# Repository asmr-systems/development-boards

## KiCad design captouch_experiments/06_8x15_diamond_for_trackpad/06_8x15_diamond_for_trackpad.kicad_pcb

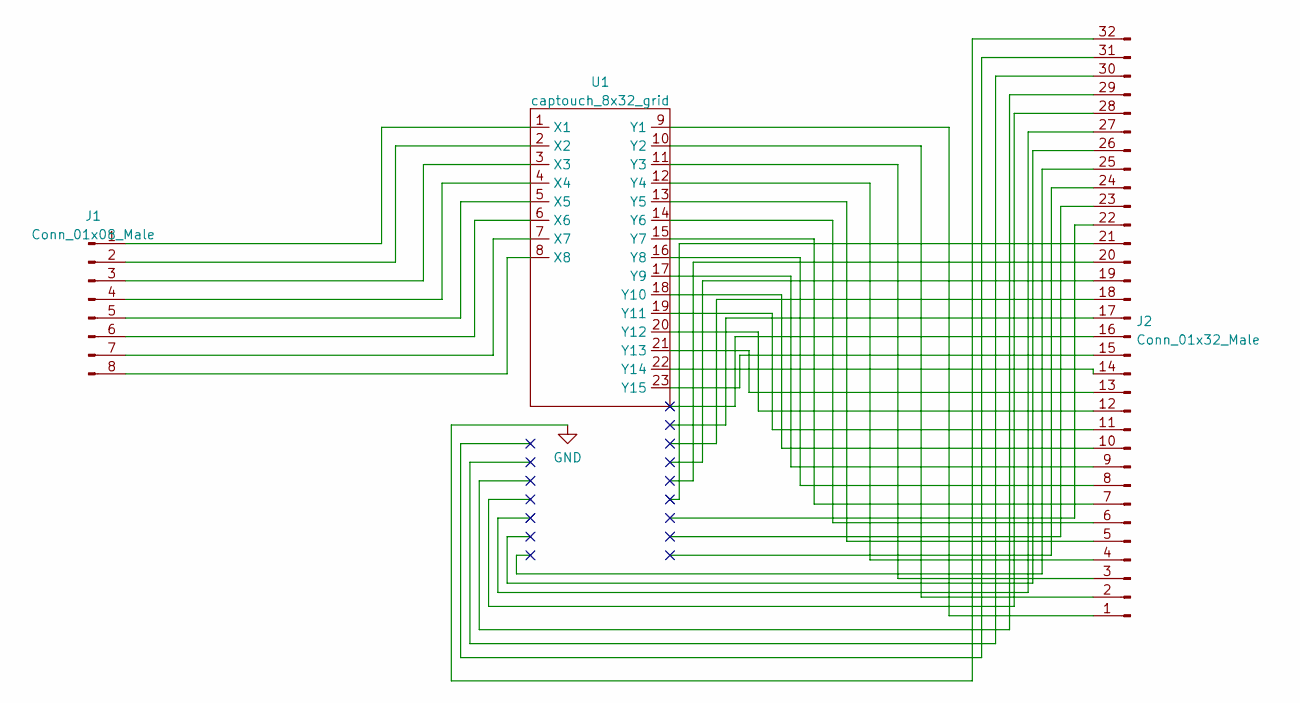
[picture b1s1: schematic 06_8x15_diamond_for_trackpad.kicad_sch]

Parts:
J1: Conn_01x08_Male; Conn_FFC_1x8_0.5mm_Molex_5019510830
J2: Conn_01x32_Male; Conn_FFC_1x32_0.5mm_Molex_5019513210
U1: captouch_8x32_grid; captouch_8x15_diamond_hatched_doubled

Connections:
GND: J2.32
unnamed: J1.1, U1.1 (X1)
unnamed: J1.2, U1.2 (X2)
unnamed: J1.3, U1.3 (X3)
unnamed: J1.4, U1.4 (X4)
unnamed: J1.5, U1.5 (X5)
unnamed: J1.6, U1.6 (X6)
unnamed: J1.7, U1.7 (X7)
unnamed: J1.8, U1.8 (X8)
unnamed: J2.1, U1.9 (Y1)
unnamed: J2.2, U1.10 (Y2)
unnamed: J2.3, U1.11 (Y3)
unnamed: J2.4, U1.12 (Y4)
unnamed: J2.5, U1.13 (Y5)
unnamed: J2.6, U1.14 (Y6)
unnamed: J2.7, U1.15 (Y7)
unnamed: J2.8, U1.16 (Y8)
unnamed: J2.9, U1.17 (Y9)
unnamed: J2.10, U1.18 (Y10)
unnamed: J2.11, U1.19 (Y11)
unnamed: J2.12, U1.20 (Y12)
unnamed: J2.13, U1.21 (Y13)
unnamed: J2.14, U1.22 (Y14)
unnamed: J2.15, U1.23 (Y15)

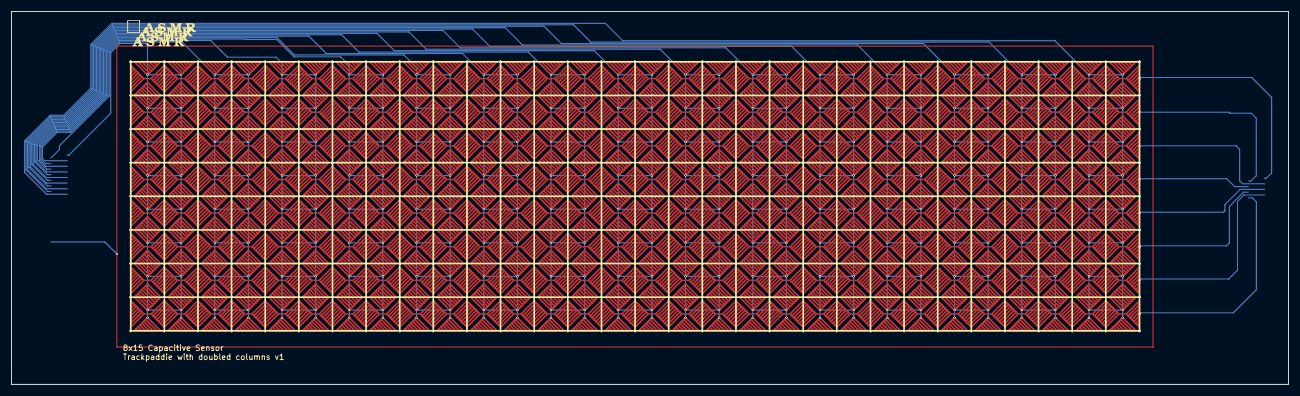
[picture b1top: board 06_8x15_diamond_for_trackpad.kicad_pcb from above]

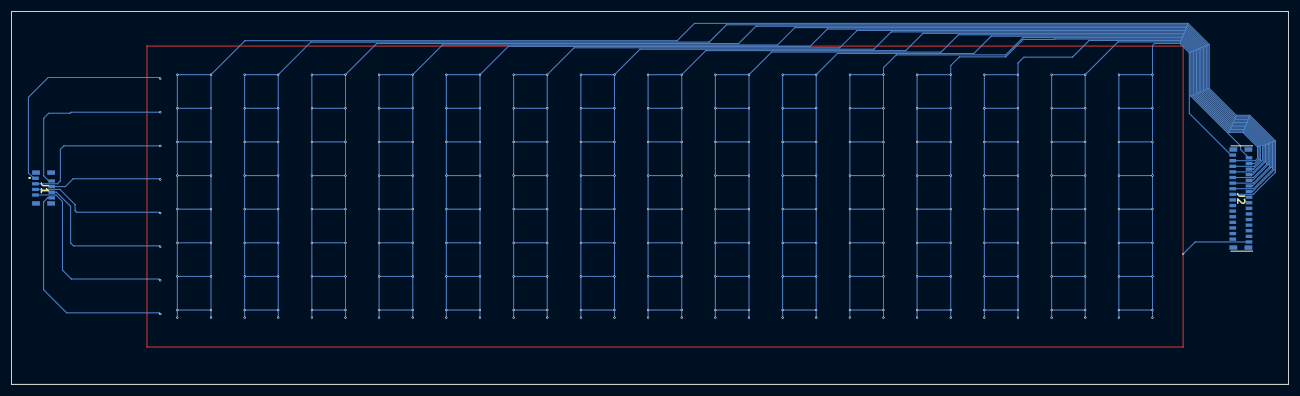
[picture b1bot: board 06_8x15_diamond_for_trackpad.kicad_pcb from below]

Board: 2 copper layers, 227.9 x 66.5 mm, 3 parts (2 on the bottom side), 23 nets.

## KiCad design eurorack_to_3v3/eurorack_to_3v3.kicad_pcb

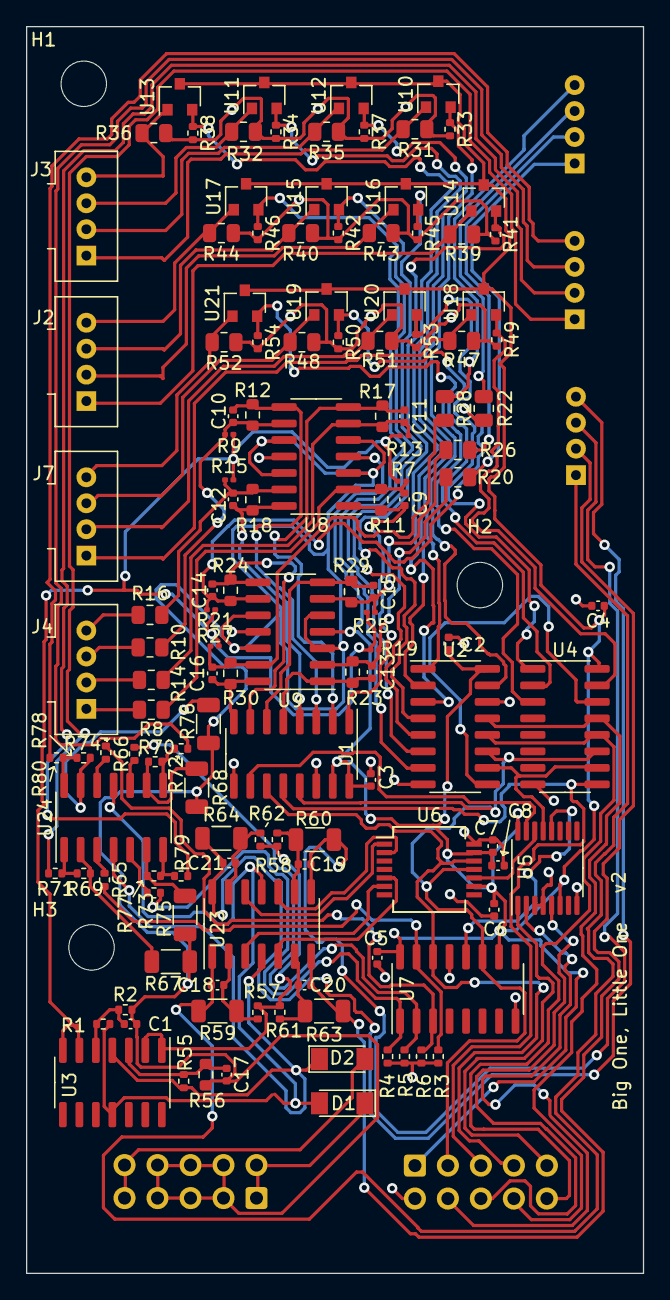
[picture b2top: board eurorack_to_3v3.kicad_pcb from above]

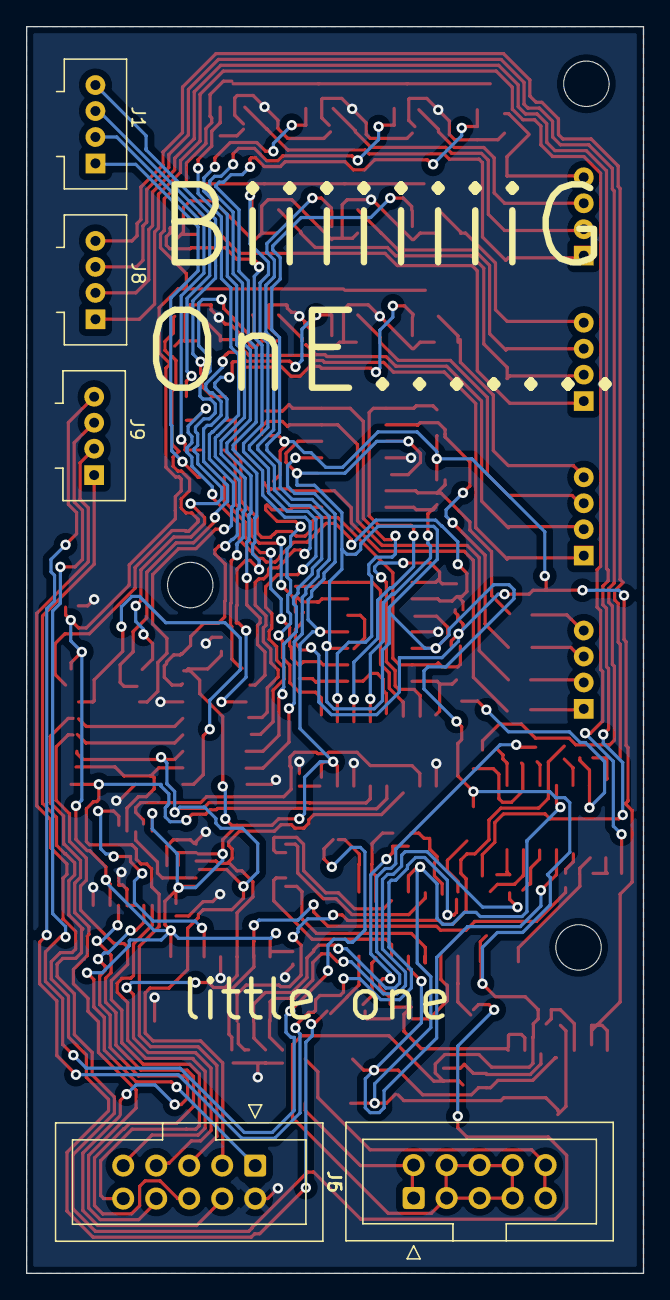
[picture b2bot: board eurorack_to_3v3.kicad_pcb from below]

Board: 2 copper layers, 47.5 x 96.0 mm, 138 parts (5 on the bottom side), 104 nets.

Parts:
C1, C2, C4, C5, C6, C7, C8, C17: 0.1uF; C_0402_1005Metric
C3: 1uF; C_0402_1005Metric
C9, C10, C11, C12, C13, C14, C15, C16, C18, C19, C20, C21: 1nF; C_0402_1005Metric
D1, D2: D; D_MiniMELF
H1, H2, H3: MountingHole; MountingHole_3.5mm
J1: cv_in_2; Connector_TE_AMP_HPI-1735446-4_1x04_P2.00mm_Vertical
J2: gate_in_2; Connector_TE_AMP_HPI-1735446-4_1x04_P2.00mm_Vertical
J3: gate_in_1; Connector_TE_AMP_HPI-1735446-4_1x04_P2.00mm_Vertical
J4: cv_in_1; Connector_TE_AMP_HPI-1735446-4_1x04_P2.00mm_Vertical
J5: Eurorack Power Header; IDC-Header_2x05_P2.54mm_Vertical
J6: Brain Bus; IDC-Header_2x05_P2.54mm_Vertical
J7: gate_in_3; Connector_TE_AMP_HPI-1735446-4_1x04_P2.00mm_Vertical
J8: gate_out; Connector_TE_AMP_HPI-1735446-4_1x04_P2.00mm_Vertical
J9: cv_out; Connector_TE_AMP_HPI-1735446-4_1x04_P2.00mm_Vertical
R1, R3, R4, R5, R6: 10K; R_0402_1005Metric
R2: 50K; R_0402_1005Metric
R7, R9, R13, R15, R19, R21, R25, R27: 200K; R_0201_0603Metric
R8, R10, R14, R16, R20, R22, R26, R28, R31, R32, R35, R36, R39, R40, R43, R44, R47, R48, R51, R52: 100K; R_0805_2012Metric
R11, R12, R17, R18, R23, R24, R29, R30: 33K; R_0603_1608Metric
R33, R34, R37, R38, R41, R42, R45, R46, R49, R50, R53, R54, R71, R72, R79, R80: 1K; R_0402_1005Metric
R55: 12K; R_0402_1005Metric
R56: 3K; R_0603_1608Metric
R57, R58, R61, R62: 11K; R_0402_1005Metric
R59, R60, R63, R64: 24K; R_1206_3216Metric
R65, R66, R73, R74: 23K; R_0402_1005Metric
R67, R68, R75, R76: 39K; R_1206_3216Metric
R69, R70, R77, R78: 56K; R_0402_1005Metric
U1: MCP3208; SOIC-16_3.9x9.9mm_P1.27mm
U2, U4: 74HC589; SOIC-16_3.9x9.9mm_P1.27mm
U3, U24: LM324; SOIC-14_3.9x8.7mm_P1.27mm
U5: 74HC137; TSSOP-16_4.4x5mm_P0.65mm
U6: BH2227FV; SSOP-14_5.3x6.2mm_P0.65mm
U7: 74HC595; SOIC-16_3.9x9.9mm_P1.27mm
U8, U9: MCP6009; SOIC-14_3.9x8.7mm_P1.27mm
U10, U11, U12, U13, U14, U15, U16, U17, U18, U19, U20, U21: MOSFET_RK7002BM; SOT-23
U23: TL074CDT; SOIC-14_3.9x8.7mm_P1.27mm

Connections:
+3V3: C2.1, C3.1, C4.1, C5.1, C6.1, C7.2, C8.1, J6.1, U1.15 (Vref), U1.16 (Vdd), U2.16 (Vcc), U4.16 (Vcc), U5.6 (E2), U5.16 (VCC), U6.9 (VDD), U6.13 (VFS), U7.10 (~SRCLR), U7.16 (VCC), U8.4 (V+), U9.4 (V+), U10.3 (Drain), U11.3 (Drain), U12.3 (Drain), U13.3 (Drain), U14.3 (Drain), U15.3 (Drain), U16.3 (Drain), U17.3 (Drain), U18.3 (Drain), U19.3 (Drain), U20.3 (Drain), U21.3 (Drain)
+12V: D2.1 (K), R55.1, U3.4 (V+), U23.4 (V+), U24.4 (V+)
-12V: D1.2 (A), R1.1, U3.11 (V-), U23.11 (V-), U24.11 (V-)
/3v3_to_cv/CV_3V3_1: U6.6 (AO4), U23.3 (+)
/3v3_to_cv/CV_3V3_2: U6.5 (AO3), U23.5 (+)
/3v3_to_cv/CV_3V3_3: U6.2 (AO2), U23.10 (+)
/3v3_to_cv/CV_3V3_4: U6.1 (AO1), U23.12 (+)
/3v3_to_cv/CV_BIAS: R57.1, R58.1, R61.1, R62.1, U3.1, U3.2 (-)
/3v3_to_cv/CV_OUT_1: C18.1, J9.1, R59.1, U23.1
/3v3_to_cv/CV_OUT_2: C20.1, J9.2, R63.1, U23.7
/3v3_to_cv/CV_OUT_3: C19.1, J9.3, R60.1, U23.8
/3v3_to_cv/CV_OUT_4: C21.1, J9.4, R64.1, U23.14
/3v3_to_gate/gate_1: R3.2, R65.2, U7.15 (QA)
/3v3_to_gate/gate_2: R4.2, R73.2, U7.1 (QB)
/3v3_to_gate/gate_3: R5.1, R66.2, U7.2 (QC)
/3v3_to_gate/gate_4: R6.2, R74.2, U7.3 (QD)
/3v3_to_gate/gate_out_1: J8.1, R71.1
/3v3_to_gate/gate_out_2: J8.2, R79.1
/3v3_to_gate/gate_out_3: J8.3, R72.1
/3v3_to_gate/gate_out_4: J8.4, R80.1
/ADC_EN: U1.10 (~CS/SHDN), U5.15 (~Y0)
/AREF_-10V: R7.2, R9.2, R13.2, R15.2, R19.2, R21.2, R25.2, R27.2, U3.6 (-), U3.7
/CS[0]: J6.9, U5.1 (A0)
/CS[1]: J6.4, U5.2 (A1)
/DAC_EN: U5.14 (~Y1), U6.10 (CSB)
/DESELECT: J6.6, U5.5 (~E1)
/GATE_IN_EN: U2.10 (~OE), U4.10 (~OE), U5.13 (~Y2)
/GATE_OUT_EN: U5.12 (~Y3), U7.12 (RCLK)
/LATCH_GATES: J6.10, U2.12 (LATCH), U4.12 (LATCH)
/LOAD_GATES: J6.8, U2.13 (~LOAD), U4.13 (~LOAD)
/PICO: J6.7, U1.11 (Din), U6.12 (DI), U7.14 (SER)
/POCI: J6.5, U1.12 (Dout), U4.9 (Qh)
/SCK: J6.3, U1.13 (CLK), U2.11 (SCLK), U4.11 (SCLK), U6.11 (CLK), U7.11 (SRCLK)
/cv_to_3v3_A/cv_3v3_1: C9.1, R11.1, U1.1 (CH0), U8.1
/cv_to_3v3_A/cv_3v3_2: C11.1, R17.1, U1.2 (CH1), U8.7
/cv_to_3v3_A/cv_3v3_3: C10.1, R12.1, U1.3 (CH2), U8.8
/cv_to_3v3_A/cv_3v3_4: C12.1, R18.1, U1.4 (CH3), U8.14
/cv_to_3v3_A/cv_in_1: J4.1, R8.1
/cv_to_3v3_A/cv_in_2: J4.2, R14.1
/cv_to_3v3_A/cv_in_3: J4.3, R10.1
/cv_to_3v3_A/cv_in_4: J4.4, R16.1
/cv_to_3v3_B/cv_3v3_1: C13.1, R23.1, U1.5 (CH4), U9.1
/cv_to_3v3_B/cv_3v3_2: C15.1, R29.1, U1.6 (CH5), U9.7
/cv_to_3v3_B/cv_3v3_3: C14.1, R24.1, U1.7 (CH6), U9.8
/cv_to_3v3_B/cv_3v3_4: C16.1, R30.1, U1.8 (CH7), U9.14
/cv_to_3v3_B/cv_in_1: J1.1, R20.1
/cv_to_3v3_B/cv_in_2: J1.2, R26.1
/cv_to_3v3_B/cv_in_3: J1.3, R22.1
/cv_to_3v3_B/cv_in_4: J1.4, R28.1
/gate_to_3v3_A/GATE_3V3_1: R33.1, U2.15 (D1), U10.2 (Source)
/gate_to_3v3_A/GATE_3V3_2: R37.1, U2.1 (D2), U12.2 (Source)
/gate_to_3v3_A/GATE_3V3_3: R34.1, U2.2 (D3), U11.2 (Source)
/gate_to_3v3_A/GATE_3V3_4: R38.1, U2.3 (D4), U13.2 (Source)
/gate_to_3v3_A/GATE_IN_1: J3.1, R31.1, U10.1 (Gate)
/gate_to_3v3_A/GATE_IN_2: J3.2, R35.1, U12.1 (Gate)
/gate_to_3v3_A/GATE_IN_3: J3.3, R32.1, U11.1 (Gate)
/gate_to_3v3_A/GATE_IN_4: J3.4, R36.1, U13.1 (Gate)
/gate_to_3v3_B/GATE_3V3_1: R41.1, U2.4 (D5), U14.2 (Source)
/gate_to_3v3_B/GATE_3V3_2: R45.1, U2.5 (D6), U16.2 (Source)
/gate_to_3v3_B/GATE_3V3_3: R42.1, U2.6 (D7), U15.2 (Source)
/gate_to_3v3_B/GATE_3V3_4: R46.1, U2.7 (D8), U17.2 (Source)
/gate_to_3v3_B/GATE_IN_1: J2.1, R39.1, U14.1 (Gate)
/gate_to_3v3_B/GATE_IN_2: J2.2, R43.1, U16.1 (Gate)
/gate_to_3v3_B/GATE_IN_3: J2.3, R40.1, U15.1 (Gate)
/gate_to_3v3_B/GATE_IN_4: J2.4, R44.1, U17.1 (Gate)
/gate_to_3v3_C/GATE_3V3_1: R49.1, U4.15 (D1), U18.2 (Source)
/gate_to_3v3_C/GATE_3V3_2: R53.1, U4.1 (D2), U20.2 (Source)
/gate_to_3v3_C/GATE_3V3_3: R50.1, U4.2 (D3), U19.2 (Source)
/gate_to_3v3_C/GATE_3V3_4: R54.1, U4.3 (D4), U21.2 (Source)
/gate_to_3v3_C/GATE_IN_1: J7.1, R47.1, U18.1 (Gate)
/gate_to_3v3_C/GATE_IN_2: J7.2, R51.1, U20.1 (Gate)
/gate_to_3v3_C/GATE_IN_3: J7.3, R48.1, U19.1 (Gate)
/gate_to_3v3_C/GATE_IN_4: J7.4, R52.1, U21.1 (Gate)
GND: C1.2, C17.2, J5.3 (GND), J5.4 (GND), J5.5 (GND), J5.6 (GND), J5.7 (GND), J5.8 (GND), R2.2, R56.2, R67.2, R68.2, R75.2, R76.2, U8.3 (+), U8.5 (+), U8.10 (+), U8.12 (+), U9.3 (+), U9.5 (+), U9.10 (+), U9.12 (+)
GNDD: C2.2, C3.2, C4.2, C5.2, C6.2, C7.1, C8.2, J6.2, R3.1, R4.1, R5.2, R6.1, R31.2, R32.2, R33.2, R34.2, R35.2, R36.2, R37.2, R38.2, R39.2, R40.2, R41.2, R42.2, R43.2, R44.2, R45.2, R46.2, R47.2, R48.2, R49.2, R50.2, R51.2, R52.2, R53.2, R54.2, U1.9 (DGND), U1.14 (AGND), U2.8 (GND), U2.14 (SER), U4.8 (GND), U5.3 (A2), U5.4 (~LE), U5.8 (GND), U6.14 (VSS), U7.8 (GND), U7.13 (~OE), U8.11 (V-), U9.11 (V-)
unnamed: C1.1, R1.2, R2.1, U3.5 (+)
unnamed: C9.2, R7.1, R8.2, R11.2, U8.2 (-)
unnamed: C10.2, R9.1, R10.2, R12.2, U8.9 (-)
unnamed: C11.2, R13.1, R14.2, R17.2, U8.6 (-)
unnamed: C12.2, R15.1, R16.2, R18.2, U8.13 (-)
unnamed: C13.2, R19.1, R20.2, R23.2, U9.2 (-)
unnamed: C14.2, R21.1, R22.2, R24.2, U9.9 (-)
unnamed: C15.2, R25.1, R26.2, R29.2, U9.6 (-)
unnamed: C16.2, R27.1, R28.2, R30.2, U9.13 (-)
unnamed: C17.1, R55.2, R56.1, U3.3 (+)
unnamed: C18.2, R57.2, R59.2, U23.2 (-)
unnamed: C19.2, R58.2, R60.2, U23.9 (-)
unnamed: C20.2, R61.2, R63.2, U23.6 (-)
unnamed: C21.2, R62.2, R64.2, U23.13 (-)
unnamed: D1.1 (K), J5.1 (-12V), J5.2 (-12V)
unnamed: D2.2 (A), J5.9 (+12V), J5.10 (+12V)
unnamed: R65.1, U24.3 (+)
unnamed: R66.1, U24.10 (+)
unnamed: R67.1, R69.2, U24.2 (-)
unnamed: R68.1, R70.2, U24.9 (-)
unnamed: R69.1, R71.2, U24.1
unnamed: R70.1, R72.2, U24.8
unnamed: R73.1, U24.5 (+)
unnamed: R74.1, U24.12 (+)
unnamed: R75.1, R77.2, U24.6 (-)
unnamed: R76.1, R78.2, U24.13 (-)
unnamed: R77.1, R79.2, U24.7
unnamed: R78.1, R80.2, U24.14
unnamed: U2.9 (Qh), U4.14 (SER)

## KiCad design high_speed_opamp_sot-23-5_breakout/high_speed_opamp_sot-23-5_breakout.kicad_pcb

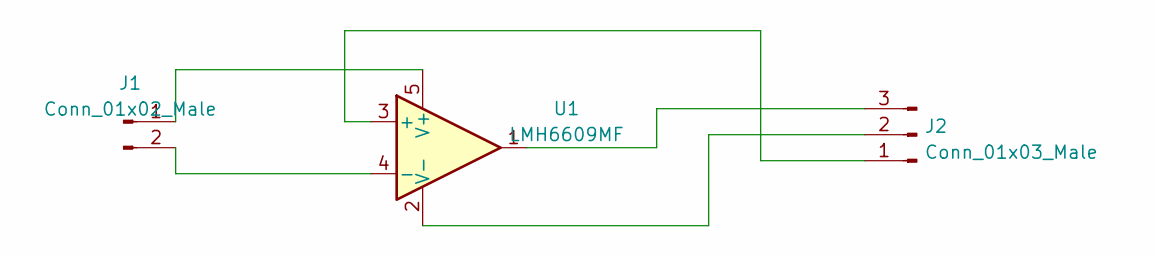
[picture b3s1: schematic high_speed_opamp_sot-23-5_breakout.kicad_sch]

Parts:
J1: Conn_01x02_Male; PinHeader_1x02_P2.54mm_Vertical
J2: Conn_01x03_Male; PinHeader_1x03_P2.54mm_Vertical
U1: LMH6609MF; SOT-23-5

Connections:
unnamed: J1.1, U1.5 (V+)
unnamed: J2.1, U1.3 (+)
unnamed: J2.2, U1.2 (V-)
unnamed: J2.3, U1.1
unnamed: J1.2, U1.4 (-)

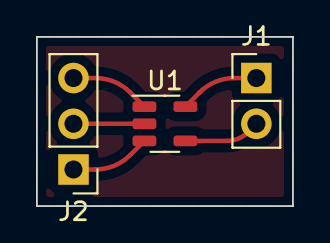
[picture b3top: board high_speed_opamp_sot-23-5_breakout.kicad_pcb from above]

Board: 2 copper layers, 14.2 x 9.4 mm, 3 parts (0 on the bottom side), 5 nets.

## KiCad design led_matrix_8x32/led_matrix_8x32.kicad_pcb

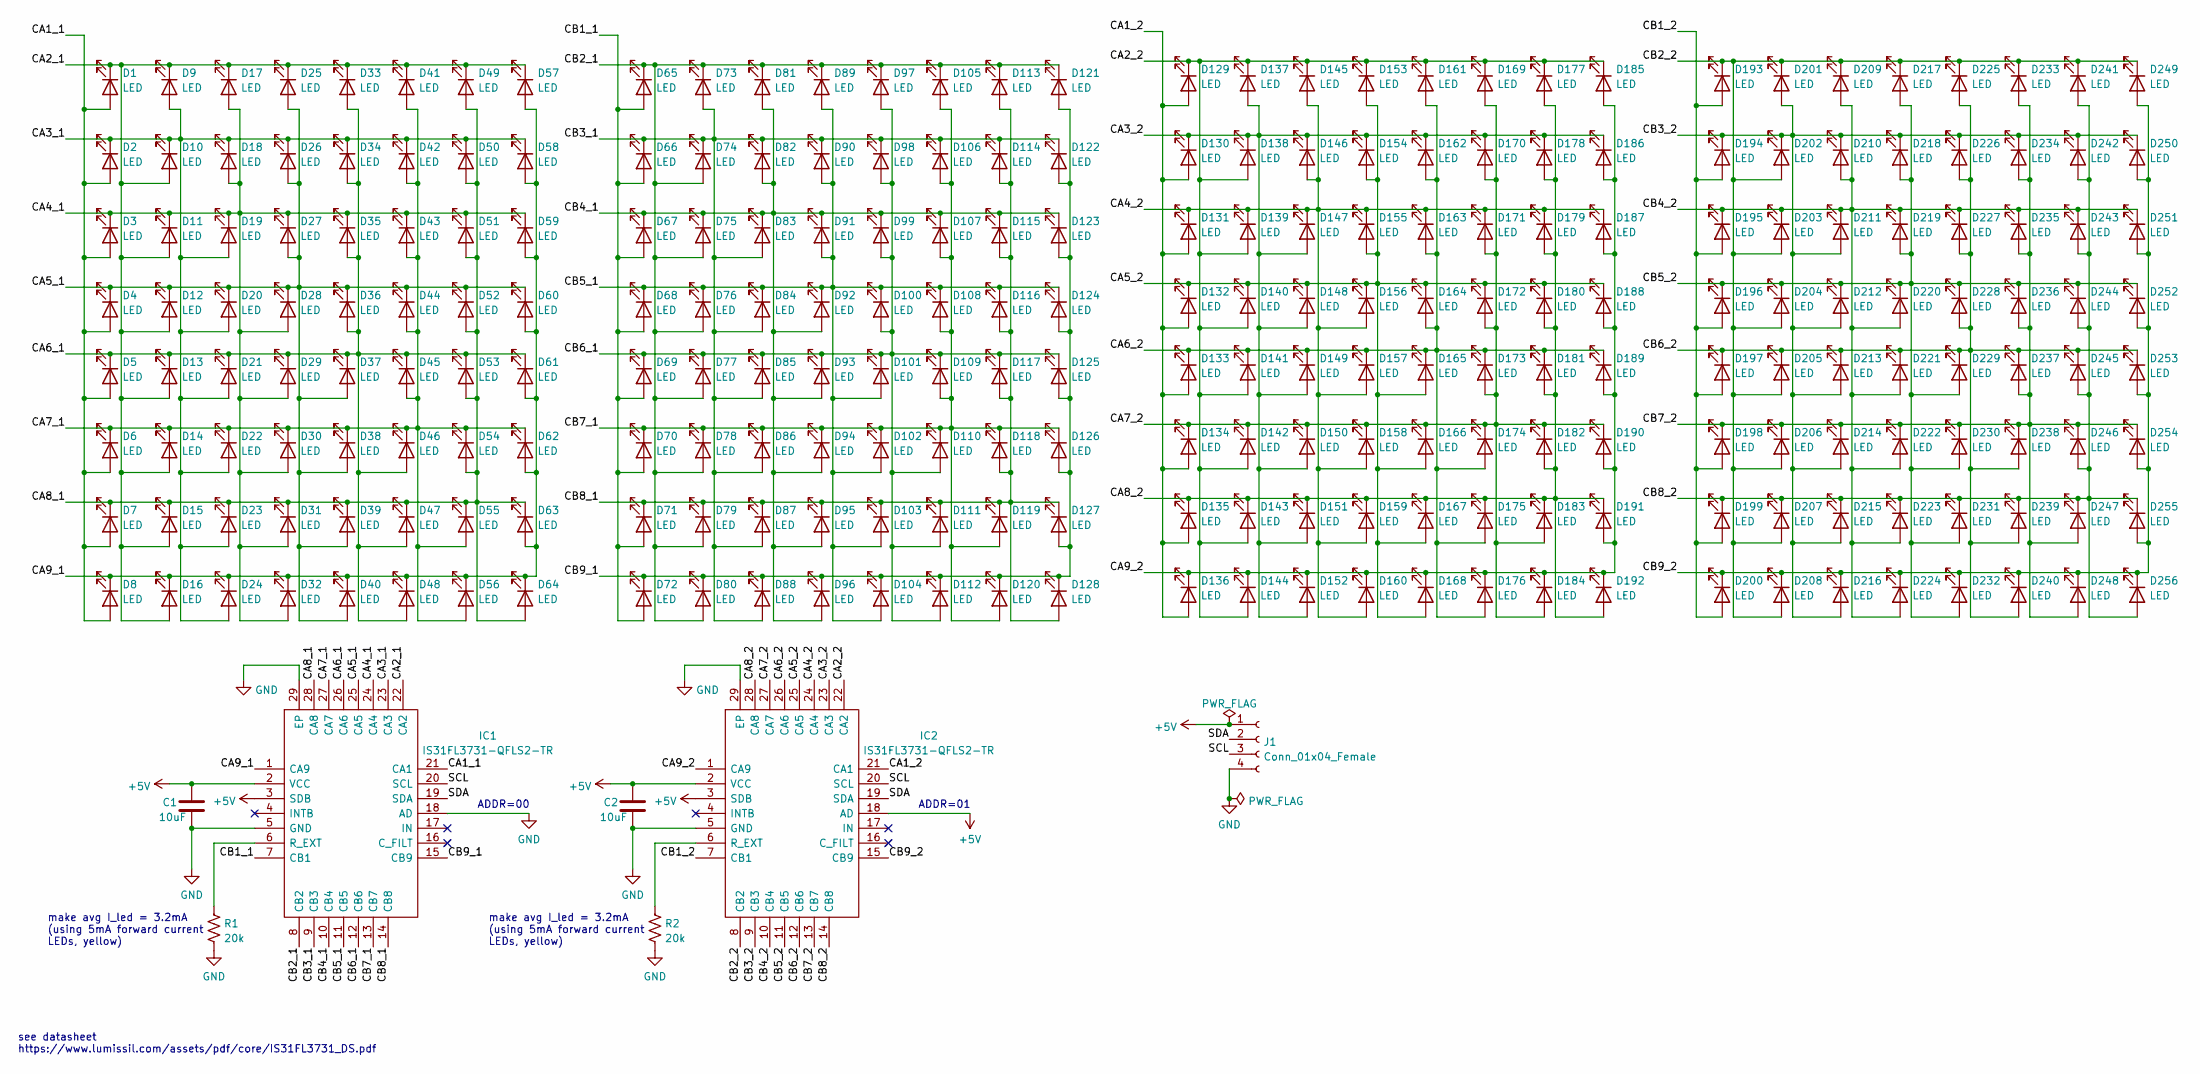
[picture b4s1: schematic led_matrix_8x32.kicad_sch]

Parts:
C1, C2: 10uF; C_0603_1608Metric
D1, D2, D3, D4, D5, D6, D7, D8, D9, D10, D11, D12, D13, D14, D15, D16, D17, D18, D19, D20, D21, D22, D23, D24, D25, D26, D27, D28, D29, D30, D31, D32, D33, D34, D35, D36, D37, D38, D39, D40, D41, D42, D43, D44, D45, D46, D47, D48, D49, D50, D51, D52, D53, D54, D55, D56, D57, D58, D59, D60, D61, D62, D63, D64, D65, D66, D67, D68, D69, D70, D71, D72, D73, D74, D75, D76, D77, D78, D79, D80, D81, D82, D83, D84, D85, D86, D87, D88, D89, D90, D91, D92, D93, D94, D95, D96, D97, D98, D99, D100, D101, D102, D103, D104, D105, D106, D107, D108, D109, D110, D111, D112, D113, D114, D115, D116, D117, D118, D119, D120, D121, D122, D123, D124, D125, D126, D127, D128, D129, D130, D131, D132, D133, D134, D135, D136, D137, D138, D139, D140, D141, D142, D143, D144, D145, D146, D147, D148, D149, D150, D151, D152, D153, D154, D155, D156, D157, D158, D159, D160, D161, D162, D163, D164, D165, D166, D167, D168, D169, D170, D171, D172, D173, D174, D175, D176, D177, D178, D179, D180, D181, D182, D183, D184, D185, D186, D187, D188, D189, D190, D191, D192, D193, D194, D195, D196, D197, D198, D199, D200, D201, D202, D203, D204, D205, D206, D207, D208, D209, D210, D211, D212, D213, D214, D215, D216, D217, D218, D219, D220, D221, D222, D223, D224, D225, D226, D227, D228, D229, D230, D231, D232, D233, D234, D235, D236, D237, D238, D239, D240, D241, D242, D243, D244, D245, D246, D247, D248, D249, D250, D251, D252, D253, D254, D255, D256: LED; LED_0603_1608Metric
IC1, IC2: IS31FL3731-QFLS2-TR; QFN40P400X400X80-29N-D; Manufacturer_Part_Number IS31FL3731-QFLS2-TR
J1: Conn_01x04_Female; PinSocket_1x04_P2.54mm_Vertical
R1, R2: 20k; R_0603_1608Metric

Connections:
+5V: C1.1, C2.1, IC1.2 (VCC), IC1.3 (SDB), IC2.2 (VCC), IC2.3 (SDB), IC2.18 (AD), J1.1
/CA1_1: D1.2 (A), D2.2 (A), D3.2 (A), D4.2 (A), D5.2 (A), D6.2 (A), D7.2 (A), D8.2 (A), IC1.21 (CA1)
/CA1_2: D129.2 (A), D130.2 (A), D131.2 (A), D132.2 (A), D133.2 (A), D134.2 (A), D135.2 (A), D136.2 (A), IC2.21 (CA1)
/CA2_1: D1.1 (K), D9.1 (K), D10.2 (A), D11.2 (A), D12.2 (A), D13.2 (A), D14.2 (A), D15.2 (A), D16.2 (A), D17.1 (K), D25.1 (K), D33.1 (K), D41.1 (K), D49.1 (K), D57.1 (K), IC1.22 (CA2)
/CA2_2: D129.1 (K), D137.1 (K), D138.2 (A), D139.2 (A), D140.2 (A), D141.2 (A), D142.2 (A), D143.2 (A), D144.2 (A), D145.1 (K), D153.1 (K), D161.1 (K), D169.1 (K), D177.1 (K), D185.1 (K), IC2.22 (CA2)
/CA3_1: D2.1 (K), D9.2 (A), D10.1 (K), D18.1 (K), D19.2 (A), D20.2 (A), D21.2 (A), D22.2 (A), D23.2 (A), D24.2 (A), D26.1 (K), D34.1 (K), D42.1 (K), D50.1 (K), D58.1 (K), IC1.23 (CA3)
/CA3_2: D130.1 (K), D137.2 (A), D138.1 (K), D146.1 (K), D147.2 (A), D148.2 (A), D149.2 (A), D150.2 (A), D151.2 (A), D152.2 (A), D154.1 (K), D162.1 (K), D170.1 (K), D178.1 (K), D186.1 (K), IC2.23 (CA3)
/CA4_1: D3.1 (K), D11.1 (K), D17.2 (A), D18.2 (A), D19.1 (K), D27.1 (K), D28.2 (A), D29.2 (A), D30.2 (A), D31.2 (A), D32.2 (A), D35.1 (K), D43.1 (K), D51.1 (K), D59.1 (K), IC1.24 (CA4)
/CA4_2: D131.1 (K), D139.1 (K), D145.2 (A), D146.2 (A), D147.1 (K), D155.1 (K), D156.2 (A), D157.2 (A), D158.2 (A), D159.2 (A), D160.2 (A), D163.1 (K), D171.1 (K), D179.1 (K), D187.1 (K), IC2.24 (CA4)
/CA5_1: D4.1 (K), D12.1 (K), D20.1 (K), D25.2 (A), D26.2 (A), D27.2 (A), D28.1 (K), D36.1 (K), D37.2 (A), D38.2 (A), D39.2 (A), D40.2 (A), D44.1 (K), D52.1 (K), D60.1 (K), IC1.25 (CA5)
/CA5_2: D132.1 (K), D140.1 (K), D148.1 (K), D153.2 (A), D154.2 (A), D155.2 (A), D156.1 (K), D164.1 (K), D165.2 (A), D166.2 (A), D167.2 (A), D168.2 (A), D172.1 (K), D180.1 (K), D188.1 (K), IC2.25 (CA5)
/CA6_1: D5.1 (K), D13.1 (K), D21.1 (K), D29.1 (K), D33.2 (A), D34.2 (A), D35.2 (A), D36.2 (A), D37.1 (K), D45.1 (K), D46.2 (A), D47.2 (A), D48.2 (A), D53.1 (K), D61.1 (K), IC1.26 (CA6)
/CA6_2: D133.1 (K), D141.1 (K), D149.1 (K), D157.1 (K), D161.2 (A), D162.2 (A), D163.2 (A), D164.2 (A), D165.1 (K), D173.1 (K), D174.2 (A), D175.2 (A), D176.2 (A), D181.1 (K), D189.1 (K), IC2.26 (CA6)
/CA7_1: D6.1 (K), D14.1 (K), D22.1 (K), D30.1 (K), D38.1 (K), D41.2 (A), D42.2 (A), D43.2 (A), D44.2 (A), D45.2 (A), D46.1 (K), D54.1 (K), D55.2 (A), D56.2 (A), D62.1 (K), IC1.27 (CA7)
/CA7_2: D134.1 (K), D142.1 (K), D150.1 (K), D158.1 (K), D166.1 (K), D169.2 (A), D170.2 (A), D171.2 (A), D172.2 (A), D173.2 (A), D174.1 (K), D182.1 (K), D183.2 (A), D184.2 (A), D190.1 (K), IC2.27 (CA7)
/CA8_1: D7.1 (K), D15.1 (K), D23.1 (K), D31.1 (K), D39.1 (K), D47.1 (K), D49.2 (A), D50.2 (A), D51.2 (A), D52.2 (A), D53.2 (A), D54.2 (A), D55.1 (K), D63.1 (K), D64.2 (A), IC1.28 (CA8)
/CA8_2: D135.1 (K), D143.1 (K), D151.1 (K), D159.1 (K), D167.1 (K), D175.1 (K), D177.2 (A), D178.2 (A), D179.2 (A), D180.2 (A), D181.2 (A), D182.2 (A), D183.1 (K), D191.1 (K), D192.2 (A), IC2.28 (CA8)
/CA9_1: D8.1 (K), D16.1 (K), D24.1 (K), D32.1 (K), D40.1 (K), D48.1 (K), D56.1 (K), D57.2 (A), D58.2 (A), D59.2 (A), D60.2 (A), D61.2 (A), D62.2 (A), D63.2 (A), D64.1 (K), IC1.1 (CA9)
/CA9_2: D136.1 (K), D144.1 (K), D152.1 (K), D160.1 (K), D168.1 (K), D176.1 (K), D184.1 (K), D185.2 (A), D186.2 (A), D187.2 (A), D188.2 (A), D189.2 (A), D190.2 (A), D191.2 (A), D192.1 (K), IC2.1 (CA9)
/CB1_1: D65.2 (A), D66.2 (A), D67.2 (A), D68.2 (A), D69.2 (A), D70.2 (A), D71.2 (A), D72.2 (A), IC1.7 (CB1)
/CB1_2: D193.2 (A), D194.2 (A), D195.2 (A), D196.2 (A), D197.2 (A), D198.2 (A), D199.2 (A), D200.2 (A), IC2.7 (CB1)
/CB2_1: D65.1 (K), D73.1 (K), D74.2 (A), D75.2 (A), D76.2 (A), D77.2 (A), D78.2 (A), D79.2 (A), D80.2 (A), D81.1 (K), D89.1 (K), D97.1 (K), D105.1 (K), D113.1 (K), D121.1 (K), IC1.8 (CB2)
/CB2_2: D193.1 (K), D201.1 (K), D202.2 (A), D203.2 (A), D204.2 (A), D205.2 (A), D206.2 (A), D207.2 (A), D208.2 (A), D209.1 (K), D217.1 (K), D225.1 (K), D233.1 (K), D241.1 (K), D249.1 (K), IC2.8 (CB2)
/CB3_1: D66.1 (K), D73.2 (A), D74.1 (K), D82.1 (K), D83.2 (A), D84.2 (A), D85.2 (A), D86.2 (A), D87.2 (A), D88.2 (A), D90.1 (K), D98.1 (K), D106.1 (K), D114.1 (K), D122.1 (K), IC1.9 (CB3)
/CB3_2: D194.1 (K), D201.2 (A), D202.1 (K), D210.1 (K), D211.2 (A), D212.2 (A), D213.2 (A), D214.2 (A), D215.2 (A), D216.2 (A), D218.1 (K), D226.1 (K), D234.1 (K), D242.1 (K), D250.1 (K), IC2.9 (CB3)
/CB4_1: D67.1 (K), D75.1 (K), D81.2 (A), D82.2 (A), D83.1 (K), D91.1 (K), D92.2 (A), D93.2 (A), D94.2 (A), D95.2 (A), D96.2 (A), D99.1 (K), D107.1 (K), D115.1 (K), D123.1 (K), IC1.10 (CB4)
/CB4_2: D195.1 (K), D203.1 (K), D209.2 (A), D210.2 (A), D211.1 (K), D219.1 (K), D220.2 (A), D221.2 (A), D222.2 (A), D223.2 (A), D224.2 (A), D227.1 (K), D235.1 (K), D243.1 (K), D251.1 (K), IC2.10 (CB4)
/CB5_1: D68.1 (K), D76.1 (K), D84.1 (K), D89.2 (A), D90.2 (A), D91.2 (A), D92.1 (K), D100.1 (K), D101.2 (A), D102.2 (A), D103.2 (A), D104.2 (A), D108.1 (K), D116.1 (K), D124.1 (K), IC1.11 (CB5)
/CB5_2: D196.1 (K), D204.1 (K), D212.1 (K), D217.2 (A), D218.2 (A), D219.2 (A), D220.1 (K), D228.1 (K), D229.2 (A), D230.2 (A), D231.2 (A), D232.2 (A), D236.1 (K), D244.1 (K), D252.1 (K), IC2.11 (CB5)
/CB6_1: D69.1 (K), D77.1 (K), D85.1 (K), D93.1 (K), D97.2 (A), D98.2 (A), D99.2 (A), D100.2 (A), D101.1 (K), D109.1 (K), D110.2 (A), D111.2 (A), D112.2 (A), D117.1 (K), D125.1 (K), IC1.12 (CB6)
/CB6_2: D197.1 (K), D205.1 (K), D213.1 (K), D221.1 (K), D225.2 (A), D226.2 (A), D227.2 (A), D228.2 (A), D229.1 (K), D237.1 (K), D238.2 (A), D239.2 (A), D240.2 (A), D245.1 (K), D253.1 (K), IC2.12 (CB6)
/CB7_1: D70.1 (K), D78.1 (K), D86.1 (K), D94.1 (K), D102.1 (K), D105.2 (A), D106.2 (A), D107.2 (A), D108.2 (A), D109.2 (A), D110.1 (K), D118.1 (K), D119.2 (A), D120.2 (A), D126.1 (K), IC1.13 (CB7)
/CB7_2: D198.1 (K), D206.1 (K), D214.1 (K), D222.1 (K), D230.1 (K), D233.2 (A), D234.2 (A), D235.2 (A), D236.2 (A), D237.2 (A), D238.1 (K), D246.1 (K), D247.2 (A), D248.2 (A), D254.1 (K), IC2.13 (CB7)
/CB8_1: D71.1 (K), D79.1 (K), D87.1 (K), D95.1 (K), D103.1 (K), D111.1 (K), D113.2 (A), D114.2 (A), D115.2 (A), D116.2 (A), D117.2 (A), D118.2 (A), D119.1 (K), D127.1 (K), D128.2 (A), IC1.14 (CB8)
/CB8_2: D199.1 (K), D207.1 (K), D215.1 (K), D223.1 (K), D231.1 (K), D239.1 (K), D241.2 (A), D242.2 (A), D243.2 (A), D244.2 (A), D245.2 (A), D246.2 (A), D247.1 (K), D255.1 (K), D256.2 (A), IC2.14 (CB8)
/CB9_1: D72.1 (K), D80.1 (K), D88.1 (K), D96.1 (K), D104.1 (K), D112.1 (K), D120.1 (K), D121.2 (A), D122.2 (A), D123.2 (A), D124.2 (A), D125.2 (A), D126.2 (A), D127.2 (A), D128.1 (K), IC1.15 (CB9)
/CB9_2: D200.1 (K), D208.1 (K), D216.1 (K), D224.1 (K), D232.1 (K), D240.1 (K), D248.1 (K), D249.2 (A), D250.2 (A), D251.2 (A), D252.2 (A), D253.2 (A), D254.2 (A), D255.2 (A), D256.1 (K), IC2.15 (CB9)
/SCL: IC1.20 (SCL), IC2.20 (SCL), J1.3
/SDA: IC1.19 (SDA), IC2.19 (SDA), J1.2
GND: C1.2, C2.2, IC1.5 (GND), IC1.18 (AD), IC1.29 (EP), IC2.5 (GND), IC2.29 (EP), J1.4, R1.2, R2.2
unnamed: IC1.6 (R_EXT), R1.1
unnamed: IC2.6 (R_EXT), R2.1

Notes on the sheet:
see datasheet https://www.lumissil.com/assets/pdf/core/IS31FL3731_DS.pdf
ADDR=01
make avg I_led = 3.2mA (using 5mA forward current LEDs, yellow)
ADDR=00

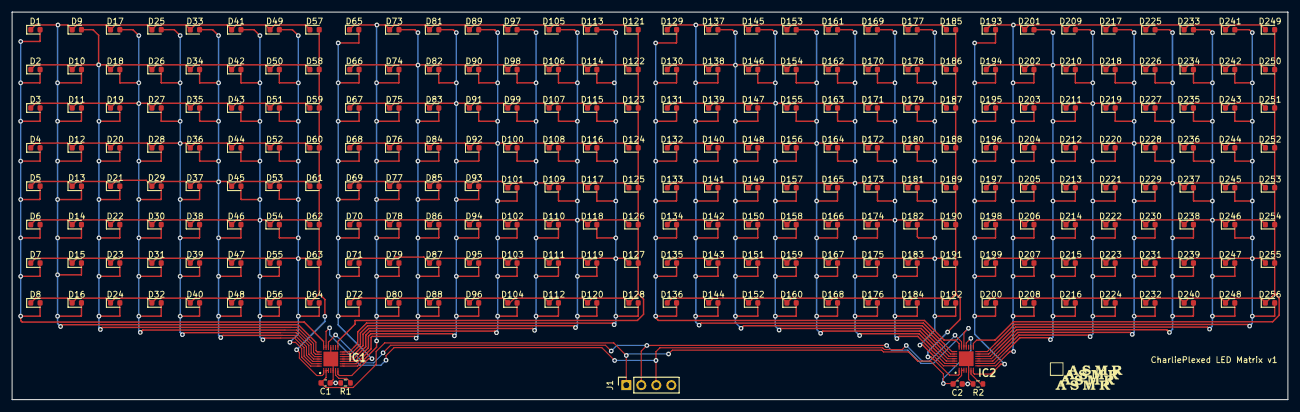
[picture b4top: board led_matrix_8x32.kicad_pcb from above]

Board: 2 copper layers, 216.0 x 65.6 mm, 263 parts (0 on the bottom side), 42 nets.

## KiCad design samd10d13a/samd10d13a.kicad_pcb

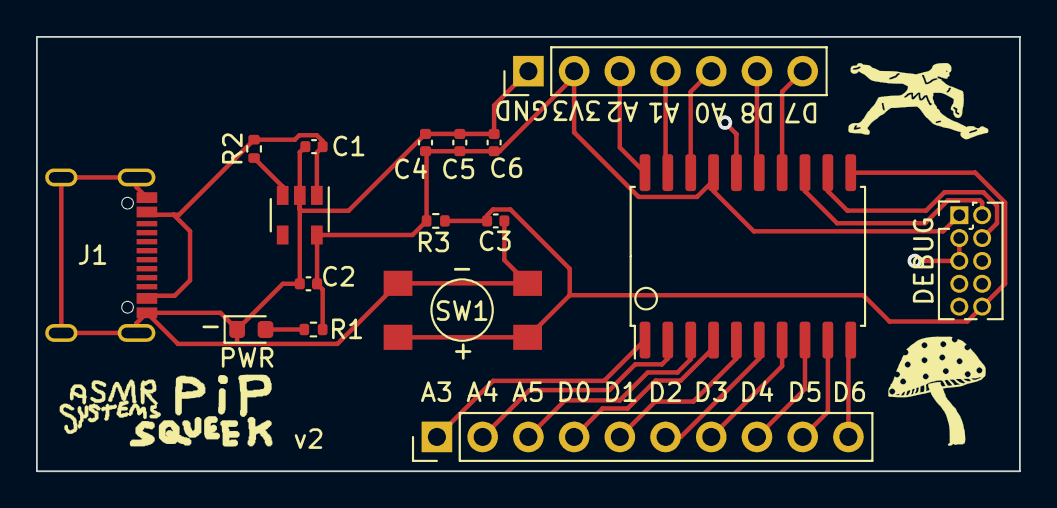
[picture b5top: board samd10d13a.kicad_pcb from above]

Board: 2 copper layers, 54.6 x 24.1 mm, 17 parts (0 on the bottom side), 23 nets.

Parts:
C1, C3, C5, C6: 0.1uF; C_0402_1005Metric
C2: 1.0uF; C_0402_1005Metric
C4: 1uF; C_0402_1005Metric
D1: LED; LED_0603_1608Metric
J1: USB_C_Receptacle_PWR_Only; USB_C_Receptacle_GCT_USB4105
J2: Conn_01x10_Male; PinHeader_1x10_P2.54mm_Vertical
J3: Conn_01x07_Male; PinHeader_1x07_P2.54mm_Vertical
J4: Conn_ARM_JTAG_SWD_10; PinHeader_2x05_P1.27mm_Vertical
R1: 100; R_0402_1005Metric
R2: 10K; R_0402_1005Metric
R3: 4.7K; R_0402_1005Metric
SW1: SW_SPST; SW_Push_TL3305
U1: NJM2866F; SOT-23-5
U2: ATSAMD10D13A-SS; SOIC-20W_7.5x12.8mm_P1.27mm

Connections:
+3V3: C2.1, C4.1, C5.1, C6.1, J3.2, J4.1, R1.1, R3.1, U1.5, U2.17
A0: J3.5, U2.18
A1: J3.4, U2.19
A2: J3.3, U2.20
A3: J2.1, U2.1
A4: J2.2, U2.2
A5: J2.3, U2.3
D0: J2.4, U2.4
D1: J2.5, U2.5
D2: J2.6, U2.6
D3: J2.7, U2.7
D4: J2.8, U2.8
D5: J2.9, U2.9
D6: J2.10, U2.10
D7: J3.7, U2.14
D8: J3.6, U2.15
GND: C1.2, C2.2, C3.2, C4.2, C5.2, C6.2, D1.1, J1.A1, J1.A12, J1.B1, J1.B12, J1.S1, J3.1, J4.3, J4.5, SW1.2, U1.2, U2.16
unnamed: D1.2, R1.2
unnamed: R2.1, U1.3
RST: C3.1, J4.10, R3.2, SW1.1, U2.11
SWCLK: J4.4, U2.12
SWDIO: J4.2, U2.13
VDD: C1.1, J1.A4, J1.A9, J1.B4, J1.B9, R2.2, U1.1

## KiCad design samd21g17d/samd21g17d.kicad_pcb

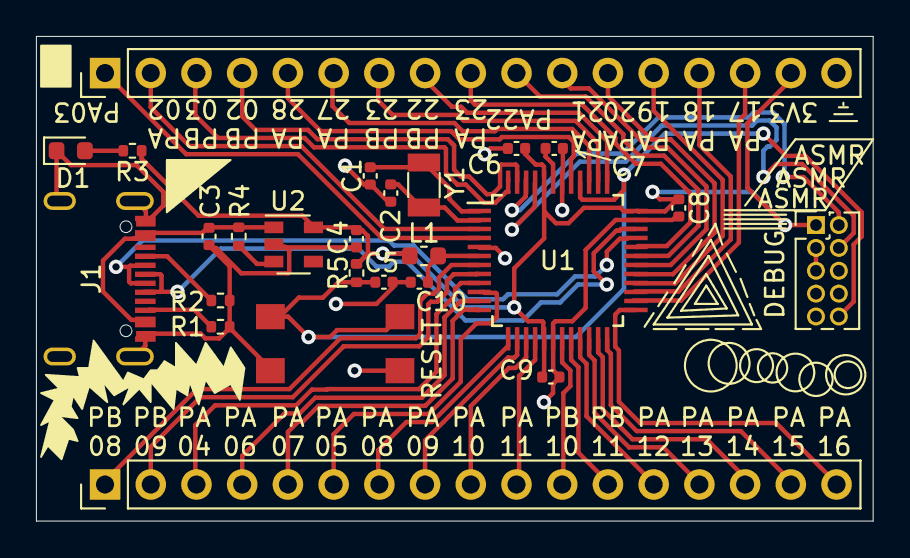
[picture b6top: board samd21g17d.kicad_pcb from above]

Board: 2 copper layers, 46.5 x 26.9 mm, 25 parts (0 on the bottom side), 48 nets.

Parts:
C1, C2: 15pF; C_0402_1005Metric
C3, C5, C6, C7, C8, C9, C10: 0.1uF; C_0402_1005Metric
C4: 1.0uF; C_0402_1005Metric
D1: LED; LED_0603_1608Metric
DEBUG: Conn_ARM_JTAG_SWD_10; PinHeader_2x05_P1.27mm_Vertical
J1: USB_C_Receptacle_USB2.0; USB_C_Receptacle_GCT_USB4105
J2, J3: Conn_01x17_Female; PinHeader_1x17_P2.54mm_Vertical
L1: FB-30Ohm; L_0603_1608Metric
R1, R2: 5.1K; R_0402_1005Metric
R3: 100; R_0402_1005Metric
R4: 10K; R_0402_1005Metric
R5: 4.7K; R_0402_1005Metric
RESET: SW_SPST; SW_Push_TL3305
U1: ATSAMD21G17D-A; TQFP-48_7x7mm_P0.5mm
U2: NJM2866F33; SOT-23-5
Y1: 32.768kHz; Crystal_SMD_3215-2Pin_3.2x1.5mm

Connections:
+3V3: C4.1, C6.1, C8.1, C9.1, DEBUG.1, J3.16, L1.1, R3.1, R5.1, U1.17, U1.36, U1.44, U2.5
D+: J1.A6, J1.B6, U1.34
D-: J1.A7, J1.B7, U1.33
GND: C1.2, C2.2, C3.2, C4.2, C5.2, C6.2, C7.2, C8.2, C9.2, C10.2, D1.1, DEBUG.3, DEBUG.5, J1.A1, J1.A12, J1.B1, J1.B12, J1.S1, J3.17, R1.2, R2.2, RESET.2, U1.5, U1.18, U1.35, U1.42, U2.2
unnamed: C7.1, U1.43
unnamed: D1.2, R3.2
unnamed: J1.A5, R2.1
unnamed: J1.B5, R1.1
unnamed: R4.1, U2.3
PA02: J3.2, U1.3
PA03: J3.1, U1.4
PA04: J2.3, U1.9
PA05: J2.6, U1.10
PA06: J2.4, U1.11
PA07: J2.5, U1.12
PA08: J2.7, U1.13
PA09: J2.8, U1.14
PA10: J2.9, U1.15
PA11: J2.10, U1.16
PA12: J2.13, U1.21
PA13: J2.14, U1.22
PA14: J2.15, U1.23
PA15: J2.16, U1.24
PA16: J2.17, U1.25
PA17: J3.15, U1.26
PA18: J3.14, U1.27
PA19: J3.13, U1.28
PA20: J3.12, U1.29
PA21: J3.11, U1.30
PA22: J3.10, U1.31
PA23: J3.9, U1.32
PA27: J3.6, U1.39
PA28: J3.5, U1.41
PB02: J3.4, U1.47
PB03: J3.3, U1.48
PB08: J2.1, U1.7
PB09: J2.2, U1.8
PB10: J2.11, U1.19
PB11: J2.12, U1.20
PB22: J3.8, U1.37
PB23: J3.7, U1.38
RESET: C5.1, DEBUG.10, R5.2, RESET.1, U1.40
SWCLK: DEBUG.4, U1.45
SWDIO: DEBUG.2, U1.46
VDD: C3.1, J1.A4, J1.A9, J1.B4, J1.B9, R4.2, U2.1
VDDA: C10.1, L1.2, U1.6
XIN32: C1.1, U1.1, Y1.1
XOUT32: C2.1, U1.2, Y1.2
